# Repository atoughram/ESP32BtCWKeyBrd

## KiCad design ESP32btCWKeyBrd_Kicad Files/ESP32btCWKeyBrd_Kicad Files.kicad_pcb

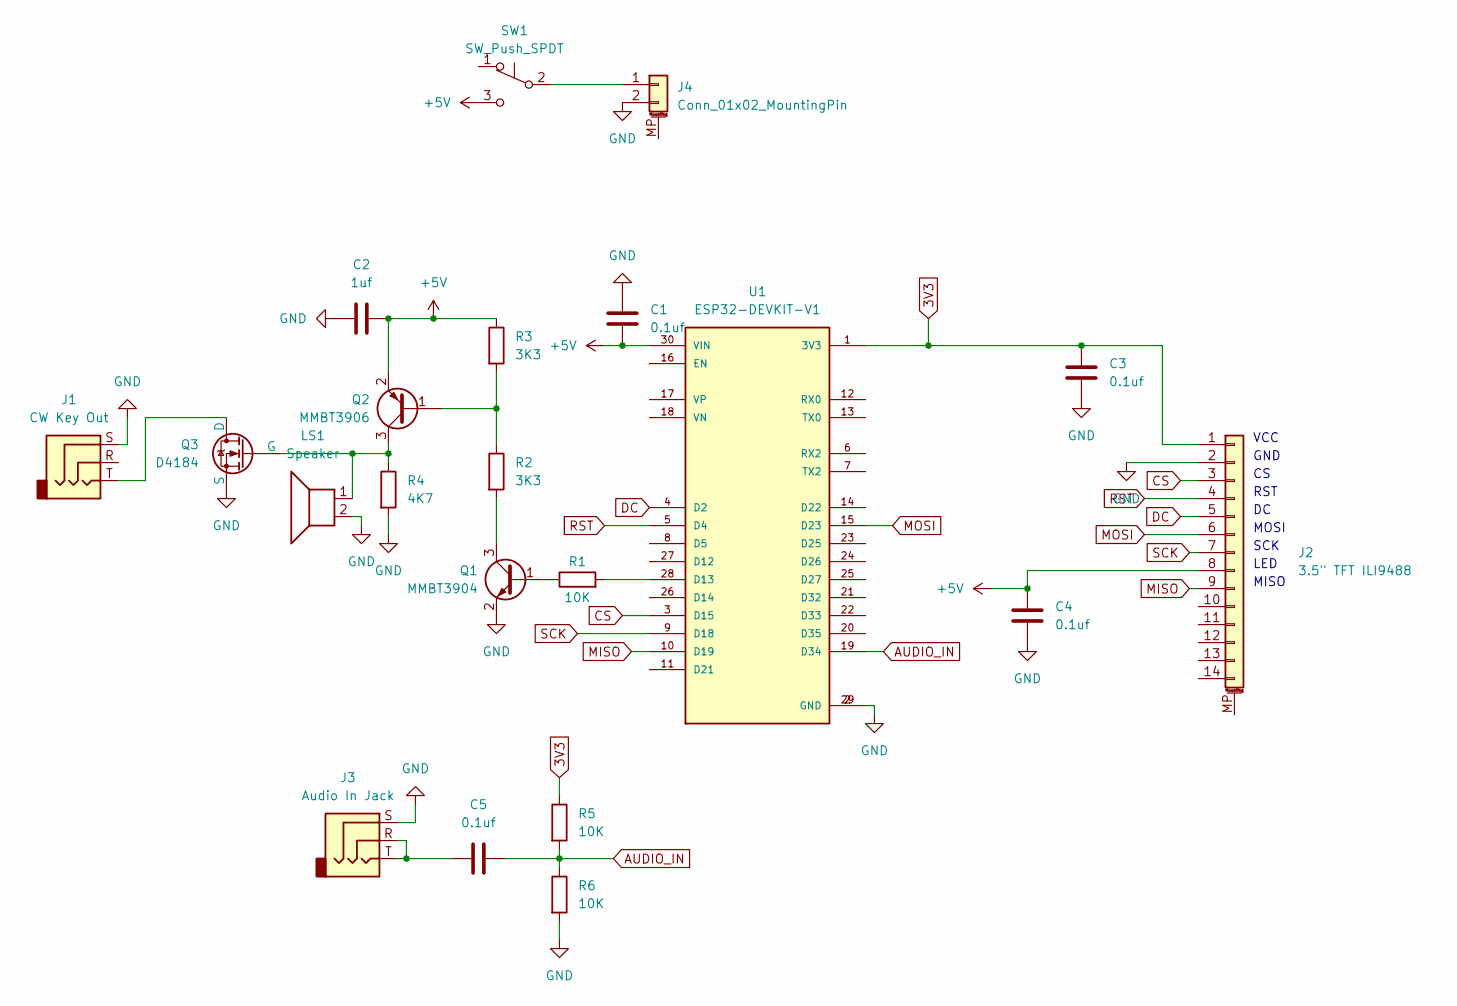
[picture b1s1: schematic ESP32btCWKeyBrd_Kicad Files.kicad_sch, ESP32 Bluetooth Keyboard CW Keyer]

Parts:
C1, C3, C4, C5: 0.1uf; C_1206_3216Metric
C2: 1uf; C_1206_3216Metric
J1: CW Key Out; Jack_3.5mm_CUI_SJ1-3525N_Horizontal
J2: 3.5" TFT ILI9488; PinHeader_1x09_P2.54mm_Vertical
J3: Audio In Jack; Jack_3.5mm_CUI_SJ1-3525N_Horizontal
J4: Conn_01x02_MountingPin; PinHeader_1x02_P2.54mm_Vertical
LS1: Speaker; Buzzer_12x9.5RM7.6
Q1: MMBT3904; SOT-23
Q2: MMBT3906; SOT-23
Q3: D4184; TO-252-3_TabPin2
R1, R5, R6: 10K; R_1206_3216Metric
R2, R3: 3K3; R_1206_3216Metric
R4: 4K7; R_1206_3216Metric
SW1: SW_Push_SPDT
U1: ESP32-DEVKIT-V1; MODULE_ESP32_DEVKIT_V1; PARTREV N/A

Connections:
3V3: C3.1, J2.1, R5.1, U1.1 (3V3)
+5V: C1.2, C2.2, C4.1, J2.8, Q2.2 (E), R3.1, SW1.3 (C), U1.30 (VIN)
AUDIO_IN: C5.2, R5.2, R6.1, U1.19 (D34)
CS: J2.3, U1.3 (D15)
DC: J2.5, U1.4 (D2)
GND: C1.1, C2.1, C3.2, C4.2, J1.S, J2.2, J3.S, J4.2, LS1.2, Q1.2 (E), Q3.3 (S), R4.2, R6.2, U1.2 (GND), U1.29 (GND)
MISO: J2.9, U1.10 (D19)
MOSI: J2.6, U1.15 (D23)
unnamed: C5.1, J3.R, J3.T
unnamed: J4.1, SW1.2 (B)
unnamed: Q1.1 (B), R1.1
unnamed: Q1.3 (C), R2.2
unnamed: Q2.1 (B), R2.1, R3.2
unnamed: LS1.1, Q2.3 (C), Q3.1 (G), R4.1
unnamed: J1.T, Q3.2 (D)
unnamed: R1.2, U1.28 (D13)
RST: J2.4, U1.5 (D4)
SCK: J2.7, U1.9 (D18)

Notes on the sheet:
LED
VCC
RST
MISO
MOSI
SCK
GND

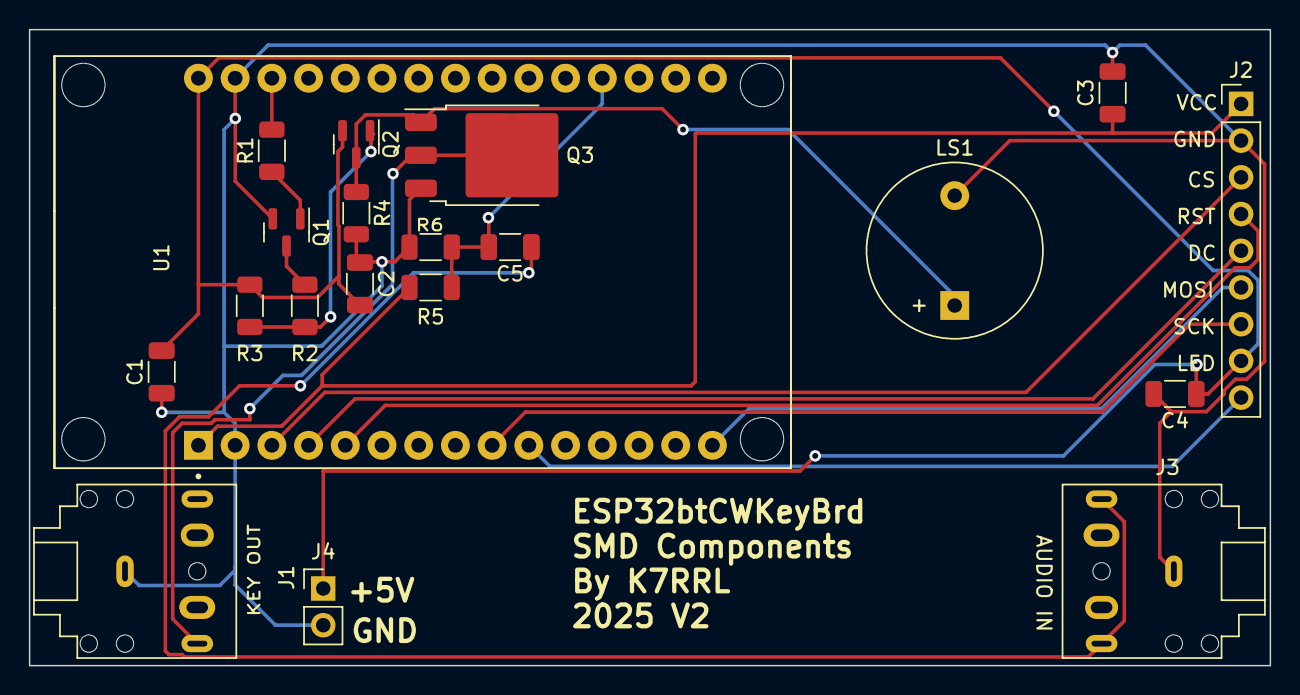
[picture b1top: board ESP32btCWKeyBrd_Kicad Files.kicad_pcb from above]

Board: 2 copper layers, 85.8 x 44.0 mm, 20 parts (0 on the bottom side), 17 nets.

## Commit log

2024-12-17 Update ro Kicad 7
    Added Schematic/PCB/Gerbers from Kicad 7
2024-12-17 End of day commit
    12-17-24 End of day Commit
2024-12-24 Incremental Commit
2024-12-25 Fixed the PCB
    Unfortunately after I ordered the original set :(
2024-12-27 Updates on drawings
2025-01-07 Initial re-commit
    Re-forked the project from jmharvey1 and added my pcb files.
